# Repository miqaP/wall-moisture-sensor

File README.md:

# wall-moisture-sensor
https://github.com/miqaP/wall-moisture-sensor

# Versionning
Pour le moment j'ai une branche dev. Comment  
- Dev -> Release 

## Version de carte
Il faut se placer du point de vue de la carte et peut-être mettre de côté l'impact sur le firmware

- MAJOR -> Modification importantes -> Changement dans les fonctionnalités du produit -> feat:
    - Ajout d'une fonctionnalitées. Est-ce que l'ajout d'un connecteur est une nouvelle fonctionnalité ? Non je ne crois pas
    - Suppression d'une fonctionnalitées

- MINOR -> Pas de modification de fonctionnalité -> design:
    - Modification de composant, qui necessite la modification du routage par exemple changement de référence d'un DC/DC -> Mais pas de changement dans la fonctionnalité
    - Optimisation du layout, déplacement des composants
    - Changement du layout pour s'intégrer dans un boitier
    - Changement de la sérigraphie
- PATCH -> Modification de la BOM -> bom
    - Ok mais des fois la modification de la BOM implique une modification du firmware, nan ?

# Continuous Integration
Voir https://sschueller.github.io/posts/ci-cd-with-kicad-and-gitlab/
https://github.com/LiveLeds/AstraDriver/tree/main

Liste des commandes qui doivent être lancées par la CI : 
- kicad-cli pcb drc wall_moisture-hardware.kicad_pcb
-  kicad-cli pcb export gerbers wall_moisture-hardware.kicad_pcb -o gerbers/
- kicad-cli render wall_moisture-hardware
- kicad-cli render wall_moisture-hardware.kicad_pcb
- kicad-cli pcb render wall_moisture-hardware.kicad_pcb
- kicad-cli pcb render wall_moisture-hardware.kicad_pcb --output 3drender/top.png -> Il faut faire les autres vues, les orientations et distances de la caméra vont dépendre de la taille du projet. Un script python pourrait determiner ces informations

L'intégration se lance lors de la création d'une release

Chose a réaliser: 
- Un rapport de release qui montre la différence entre la version actuelle et la version précedente -> Voir Kicad-diff
    - Il faut pouvoir détérminer la version précédente, comment faire ?
- Exporter les pdf des schémas et du hardware ( les couches du PCB et la carte complète)

# Note sur la configuration du projet
Commitlint s’exécute à chaque commit grâce au hook Git commit-msg. Ce hook est un script situé dans le dossier .git/hooks/commit-msg qui est automatiquement lancé par Git à la validation d’un commit. Ce script appelle Commitlint pour vérifier que le message du commit respecte les règles définies.

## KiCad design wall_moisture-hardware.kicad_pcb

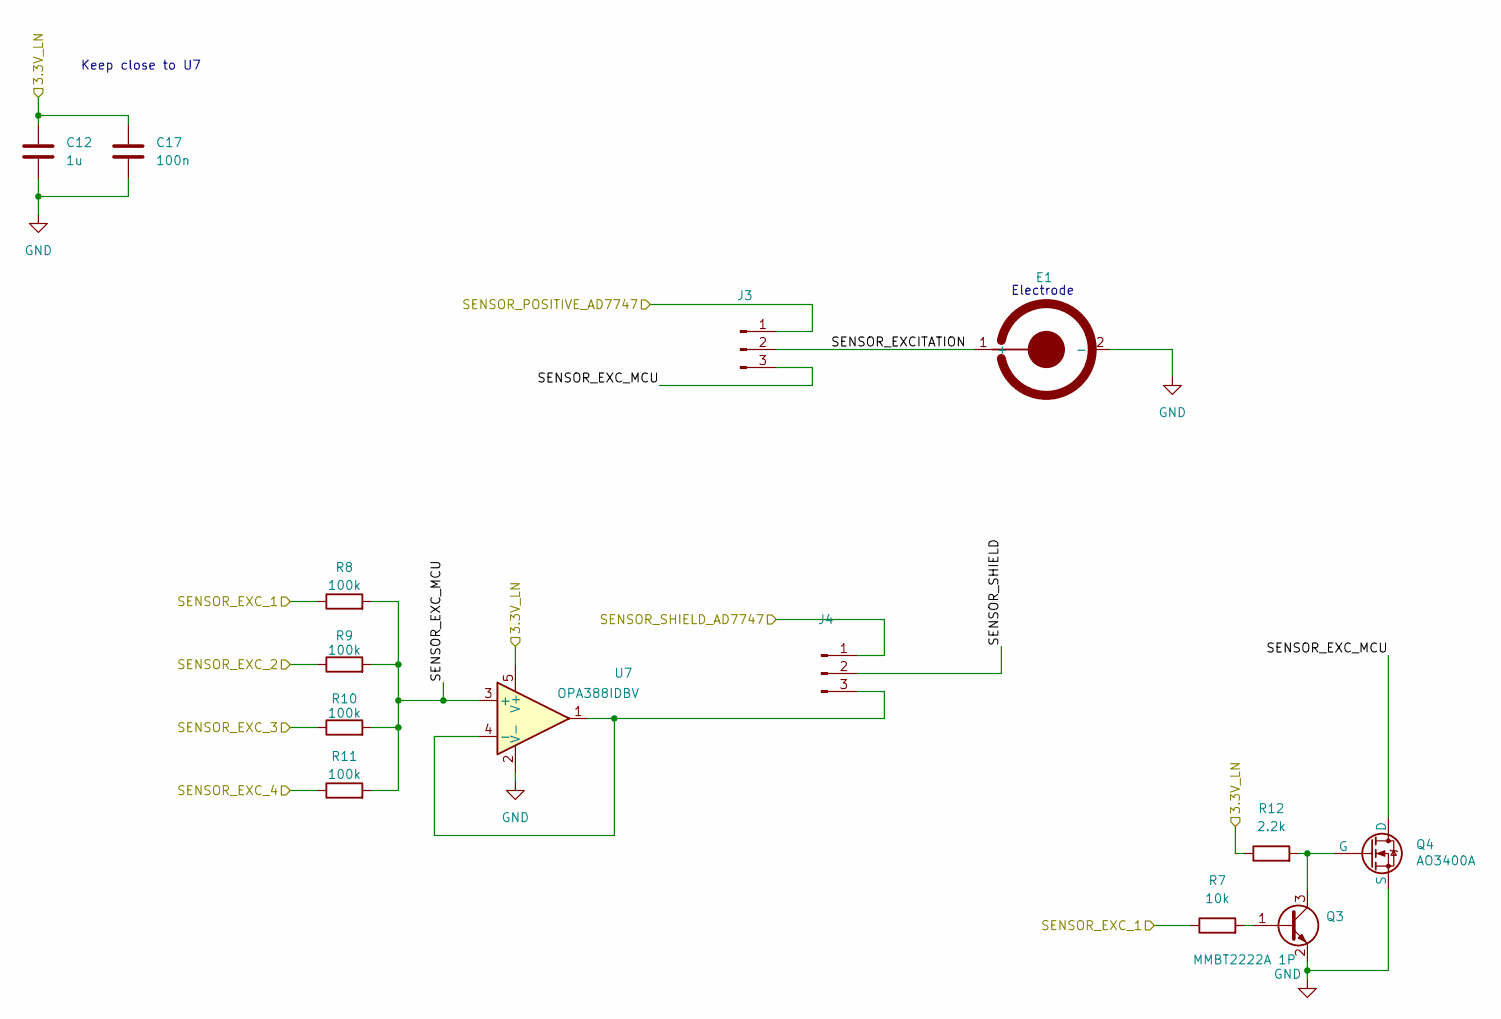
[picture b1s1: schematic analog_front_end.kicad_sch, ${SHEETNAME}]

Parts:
C12: 1u; C_0603_1608Metric; LCSC C15849
C17: 100n; C_0603_1608Metric; LCSC C14663
E1: CapacitiveElectrode-round_20mmx70mm
J3, J4: PinHeader_1x03_P2.54mm_Vertical; MPN 2541WV-03P; LCSC C5383112
Q3: SOT-23; MPN MMBT2222A 1P; LCSC C8512
Q4: SOT-23; MPN AO3400A; LCSC C20917
R7: 10k; R_0603_1608Metric; LCSC C25804
R8, R9, R10, R11: 100k; R_0603_1608Metric; LCSC C25803
R12: 2.2k; R_0603_1608Metric; LCSC C4190
U7: SOT-23-5; MPN OPA388IDBV; LCSC C1850240

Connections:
/Analog frontend/3.3V_LN: C12.1, C17.1, R12.1, U7.5 (V+); also elsewhere on the board
/Analog frontend/SENSOR_EXCITATION: E1.1 (+), J3.2
/Analog frontend/SENSOR_EXC_MCU: J3.3, Q4.1 (D), R8.2, R9.2, R10.2, R11.2, U7.3 (+)
/Analog frontend/SENSOR_POSITIVE_AD7747: J3.1; also elsewhere on the board
/Analog frontend/SENSOR_SHIELD: J4.2
/Analog frontend/SENSOR_SHIELD_AD7747: J4.1; also elsewhere on the board
/µC and digital/TIM1_CH1: R7.1, R8.1; also elsewhere on the board
/µC and digital/TIM1_CH2: R9.1; also elsewhere on the board
/µC and digital/TIM1_CH3: R10.1; also elsewhere on the board
/µC and digital/TIM1_CH4: R11.1; also elsewhere on the board
GND: C12.2, C17.2, E1.2 (-), Q3.2 (E), Q4.3 (S), U7.2 (V-); also elsewhere on the board
unnamed: J4.3, U7.1, U7.4 (-)
unnamed: Q3.1 (B), R7.2
unnamed: Q3.3 (C), Q4.2 (G), R12.2

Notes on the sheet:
Keep close to U7
Electrode

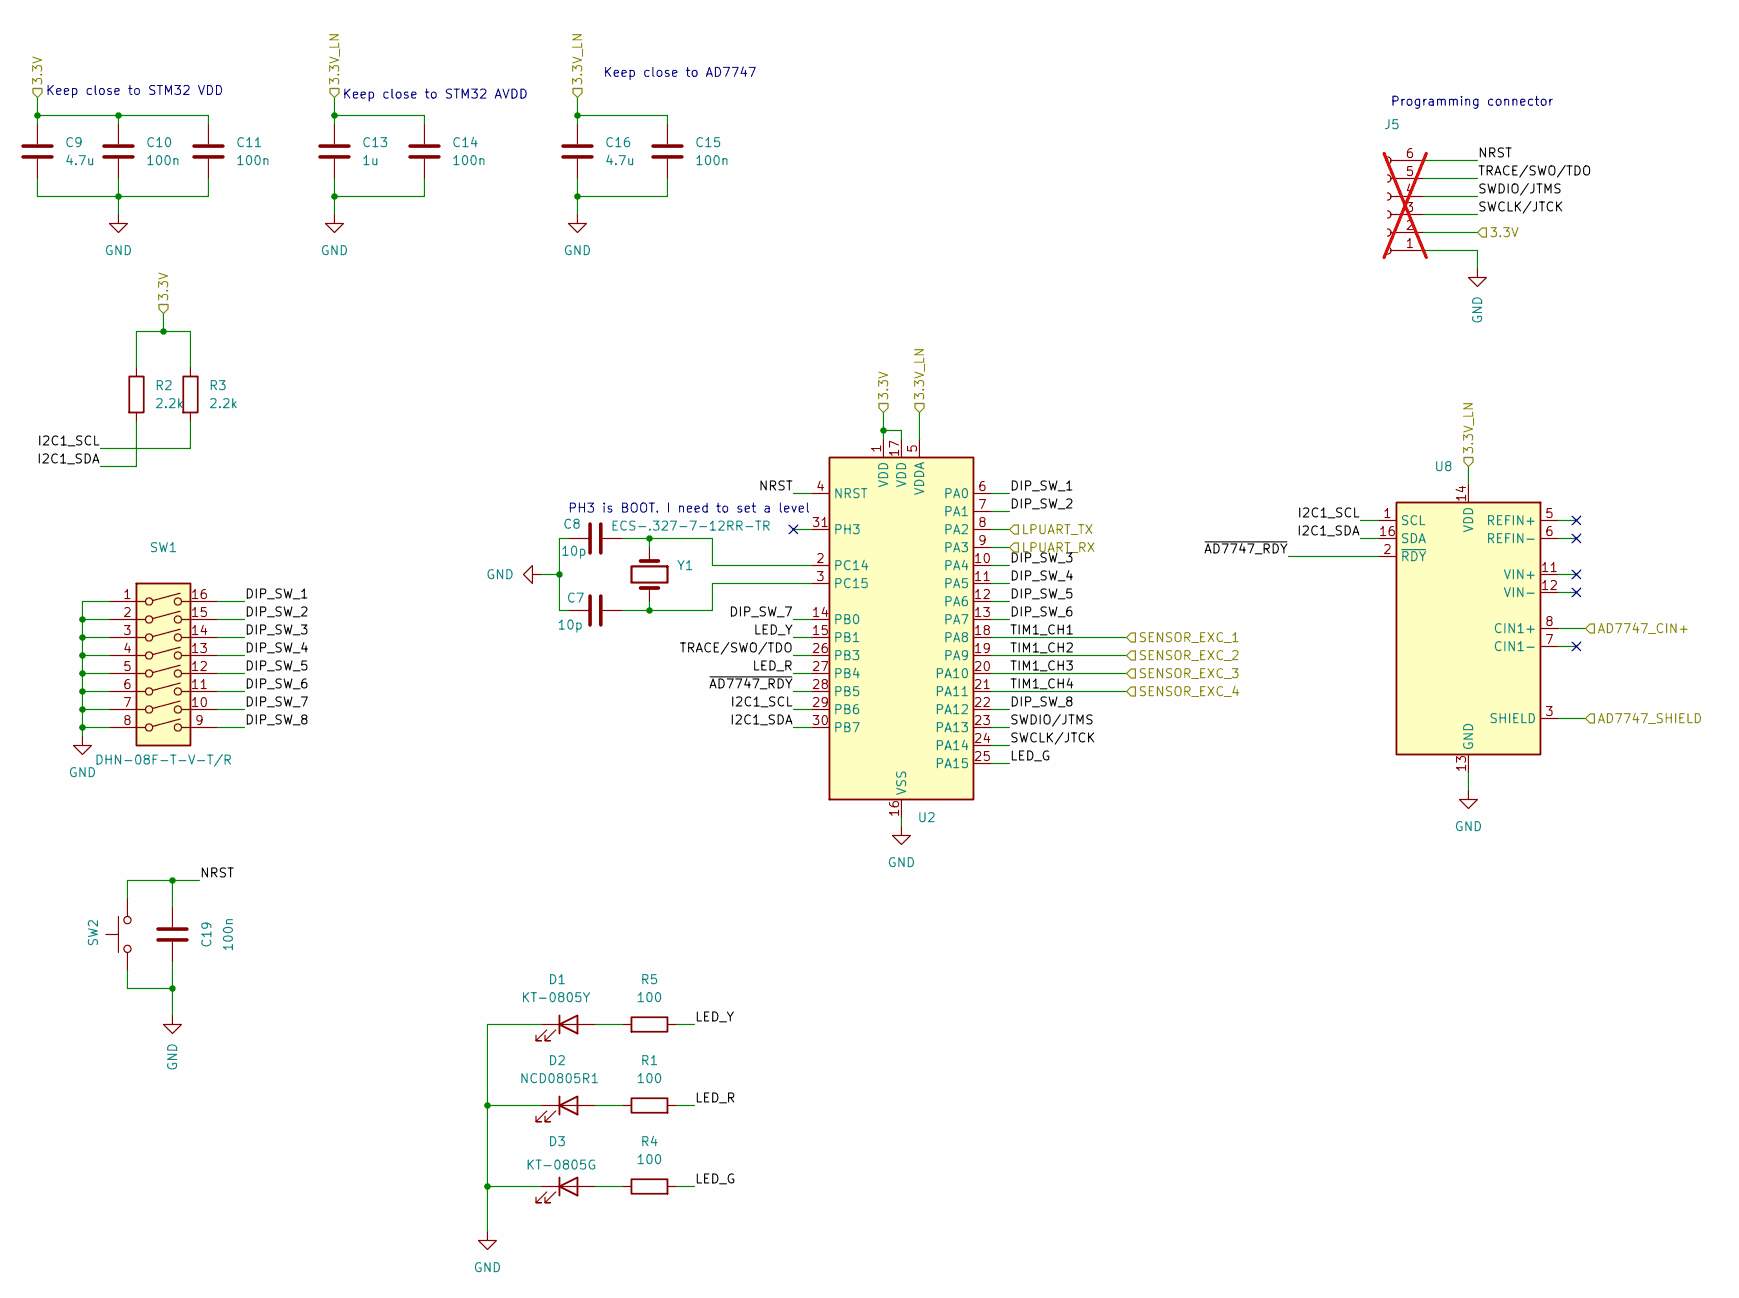
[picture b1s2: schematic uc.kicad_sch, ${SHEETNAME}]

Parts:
C7, C8: 10p; C_0603_1608Metric; LCSC C1634
C9, C16: 4.7u; C_0603_1608Metric; LCSC C19666
C10, C11, C14, C15, C19: 100n; C_0603_1608Metric; LCSC C14663
C13: 1u; C_0603_1608Metric; LCSC C15849
D1: LED_0805_2012Metric; MPN KT-0805Y; LCSC C2296
D2: LED_0805_2012Metric; MPN NCD0805R1; LCSC C84256
D3: LED_0805_2012Metric; MPN KT-0805G; LCSC C2297
J5: Skedd490107670612_2x06_P2.54mm_Debug; MPN 490107670612; not fitted
R1, R4, R5: 100; R_0603_1608Metric; LCSC C22775
R2, R3: 2.2k; R_0603_1608Metric; LCSC C4190
SW1: SW_DIP_SPSTx08_Slide_KingTek_DSHP08TJ_W5.25mm_P1.27mm_JPin; MPN DHN-08F-T-V-T/R; LCSC C89711
SW2: FSMH; SW_Push_1P1T_XKB_TS-1187A; MPN TS-1187A-B-A-B; LCSC C318884
U2: QFN-32-1EP_5x5mm_P0.5mm_EP3.45x3.45mm; MPN STM32L432KBUx; LCSC C2928224
U8: TSSOP-16_4.4x5mm_P0.65mm; MPN AD7747ARUZ; LCSC C578507
Y1: Crystal_SMD_2012-2Pin_2.0x1.2mm; MPN ECS-.327-7-12RR-TR; LCSC C2450089

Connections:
/Analog frontend/3.3V_LN: C13.1, C14.1, C15.1, C16.1, U2.5 (VDDA), U8.14 (VDD); also elsewhere on the board
/Analog frontend/SENSOR_POSITIVE_AD7747: U8.8 (CIN1+); also elsewhere on the board
/Analog frontend/SENSOR_SHIELD_AD7747: U8.3 (SHIELD); also elsewhere on the board
/Connectors and Power/3.3V: C9.1, C10.1, C11.1, J5.2, R2.1, R3.1, U2.1 (VDD), U2.17 (VDD); also elsewhere on the board
/Connectors and Power/MASTER_RX: U2.8 (PA2); also elsewhere on the board
/Connectors and Power/MASTER_TX: U2.9 (PA3); also elsewhere on the board
/µC and digital/DIP_SW_1: SW1.16, U2.6 (PA0)
/µC and digital/DIP_SW_2: SW1.15, U2.7 (PA1)
/µC and digital/DIP_SW_3: SW1.14, U2.10 (PA4)
/µC and digital/DIP_SW_4: SW1.13, U2.11 (PA5)
/µC and digital/DIP_SW_5: SW1.12, U2.12 (PA6)
/µC and digital/DIP_SW_6: SW1.11, U2.13 (PA7)
/µC and digital/DIP_SW_7: SW1.10, U2.14 (PB0)
/µC and digital/DIP_SW_8: SW1.9, U2.22 (PA12)
/µC and digital/I2C1_SCL: R3.2, U2.29 (PB6), U8.1 (SCL)
/µC and digital/I2C1_SDA: R2.2, U2.30 (PB7), U8.16 (SDA)
/µC and digital/LED_G: R4.2, U2.25 (PA15)
/µC and digital/LED_R: R1.2, U2.27 (PB4)
/µC and digital/LED_Y: R5.1, U2.15 (PB1)
/µC and digital/NRST: C19.2, J5.6, SW2.2, U2.4 (NRST)
/µC and digital/SWCLK/JTCK: J5.3, U2.24 (PA14)
/µC and digital/SWDIO/JTMS: J5.4, U2.23 (PA13)
/µC and digital/TIM1_CH1: U2.18 (PA8); also elsewhere on the board
/µC and digital/TIM1_CH2: U2.19 (PA9); also elsewhere on the board
/µC and digital/TIM1_CH3: U2.20 (PA10); also elsewhere on the board
/µC and digital/TIM1_CH4: U2.21 (PA11); also elsewhere on the board
/µC and digital/TRACE/SWO/TDO: J5.5, U2.26 (PB3)
/µC and digital/~AD7747_RDY: U2.28 (PB5), U8.2 (~RDY)
GND: C7.1, C8.1, C9.2, C10.2, C11.2, C13.2, C14.2, C15.2, C16.2, C19.1, D1.1 (K), D2.1 (K), D3.1 (K), J5.1, SW1.1, SW1.2, SW1.3, SW1.4, SW1.5, SW1.6, SW1.7, SW1.8, SW2.1, U2.16 (VSS), U2.32 (VSS), U2.33 (VSS), U8.13 (GND); also elsewhere on the board
unnamed: D1.2 (A), R5.2
unnamed: D2.2 (A), R1.1
unnamed: D3.2 (A), R4.1
unnamed: C8.2, U2.2 (PC14), Y1.1
unnamed: C7.2, U2.3 (PC15), Y1.2

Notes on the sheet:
Keep close to STM32 VDD
Programming connector
Keep close to AD7747
Keep close to STM32 AVDD
PH3 is BOOT. I need to set a level

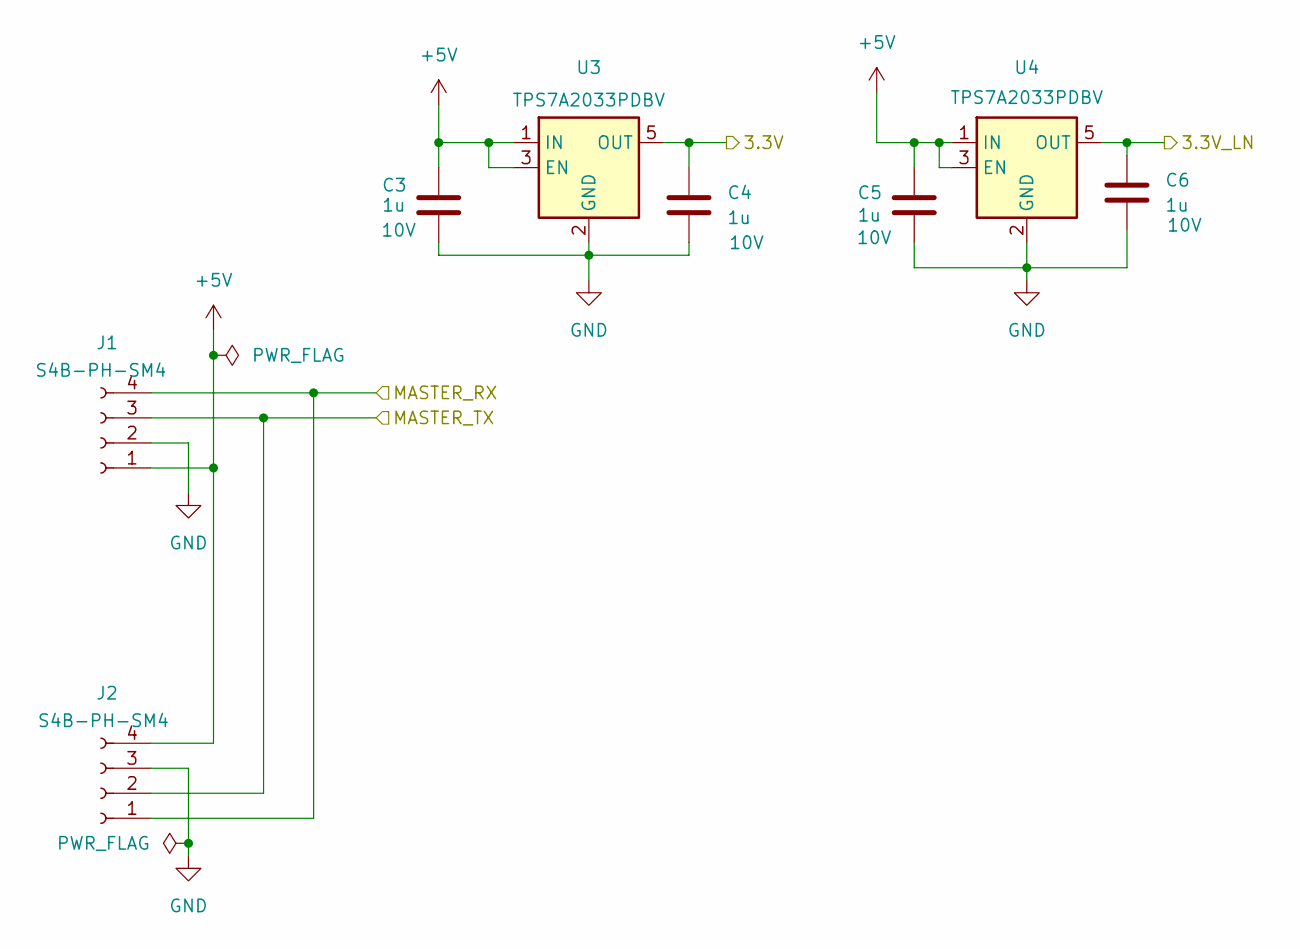
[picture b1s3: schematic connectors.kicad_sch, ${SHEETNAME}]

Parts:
C3, C4, C5, C6: 1u; C_0603_1608Metric; LCSC C15849
J1, J2: JST_PH_S4B-PH-SM4-TB_1x04-1MP_P2.00mm_Horizontal; MPN S4B-PH-SM4; LCSC C265102
U3, U4: SOT-23-5; MPN TPS7A2033PDBV; LCSC C2862740

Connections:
+5V: C3.1, C5.1, J1.1, J2.4, U3.1 (IN), U3.3 (EN), U4.1 (IN), U4.3 (EN)
/Analog frontend/3.3V_LN: C6.1, U4.5 (OUT); also elsewhere on the board
/Connectors and Power/3.3V: C4.1, U3.5 (OUT); also elsewhere on the board
/Connectors and Power/MASTER_RX: J1.4, J2.1; also elsewhere on the board
/Connectors and Power/MASTER_TX: J1.3, J2.2; also elsewhere on the board
GND: C3.2, C4.2, C5.2, C6.2, J1.2, J2.3, U3.2 (GND), U4.2 (GND); also elsewhere on the board

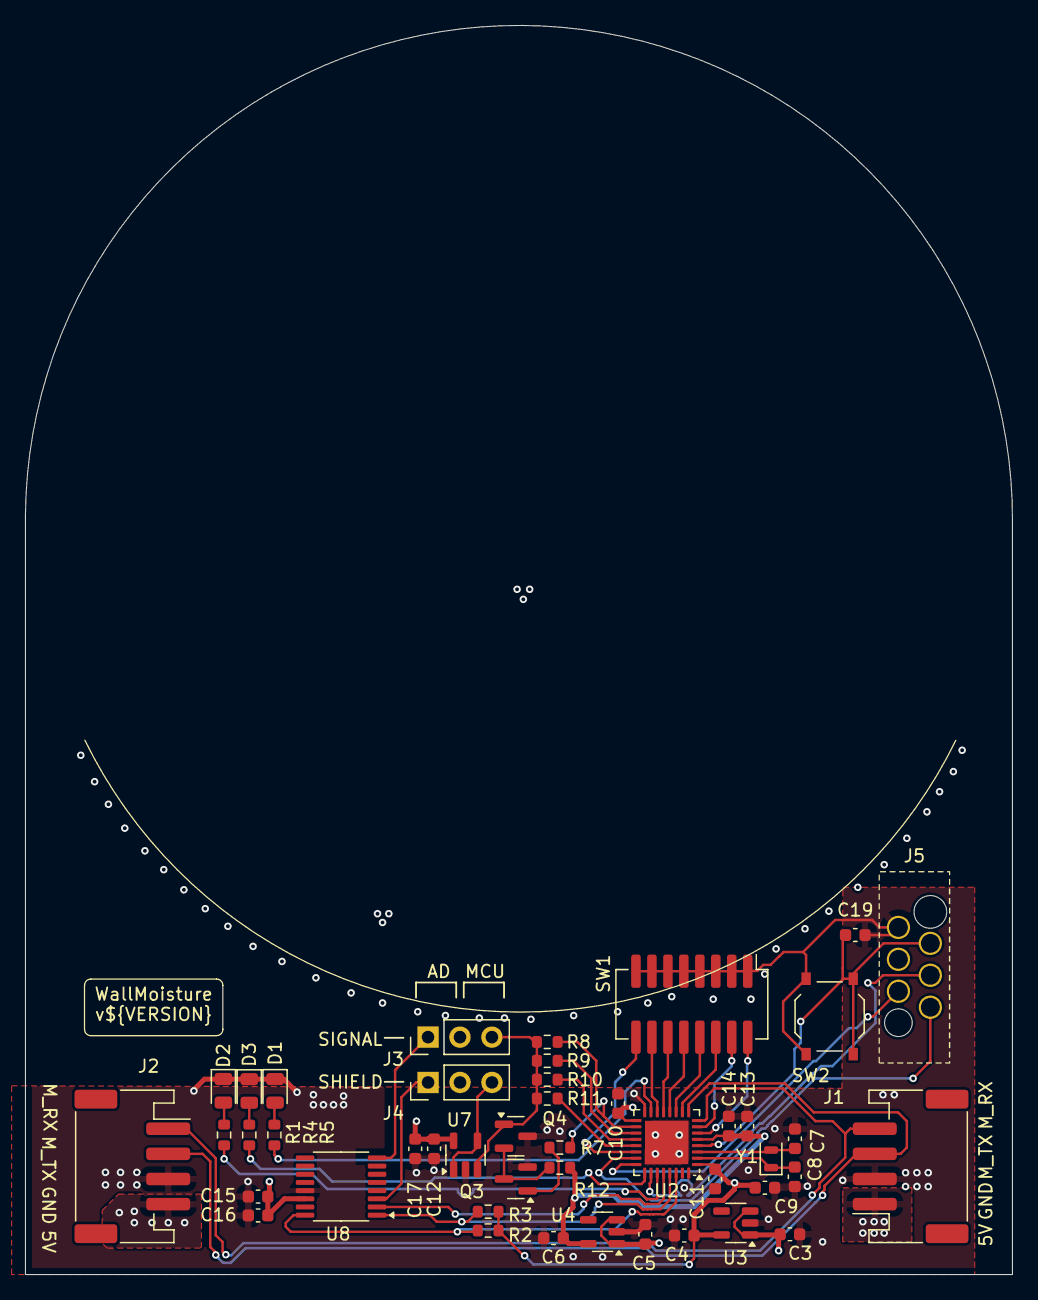
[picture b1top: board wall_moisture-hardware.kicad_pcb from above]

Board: 4 copper layers, 78.5 x 99.3 mm, 46 parts (1 on the bottom side), 40 nets.

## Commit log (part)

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2025-04-05 First commit :
2025-05-05 ci: Initial the CI
    Use https://github.com/LiveLeds/AstraDriver.git as base configuration
2025-05-05 ci: Fix project file path
2025-05-05 ci: Attempt to fix project name variable expansion and add templates
2025-05-05 ci: fix kibot relative paths and upgrade to kibot dk9
2025-05-05 ci: Fix the layer names, change dimensions for drawings
2025-05-05 ci: refactor workflows to place all the 3D render configuration next to each other
2025-05-05 ci: Attempt to fix a variable not expansed while building Jekyll
2025-05-05 ci: fix pcb pdf path
2025-05-05 ci: fix variables not expanded in Jekyll build step
2025-05-06 ci: deploy site on Netlify instead of github pages
2025-05-14 Extract Jekyll and github action configuration from the same project.yml file
2025-05-14 Fix board cutt layer
2025-05-14 Fix variable substitution in Build jekyll step
2025-05-14 Remove theme applied on report step and change the CI to uses kibot instead of running custom script which use SSH key
2025-05-14 Fix CI variable expansion
2025-05-14 ci: remove useless plugin and attempt to fix the variable sharing between the ci and jekyll
2025-05-14 ci: fix path of generated markdown file
2025-05-14 ci: Fix jekyll base url because the site is currently deployed at the root of netlify
2025-05-14 ci: attempt to add renders, schemtics and assembly variants in the project field
2025-05-15 ci: Add actions for others branches
2025-05-15 ci: attempt to add semantic release in ci workflow
2025-05-15 git: update .gitignore to ignore node and gem files
2025-05-15 silk: add board name and placeholder to version number
2025-05-15 ci: fix triggers for github actions
2025-05-15 ci: github action on dev push must fail if errors exist on the DRC / ERC
2025-05-15 ci: allow workflow to complete even on step errors, then summarize failures
2025-05-17 rule-check: Fix the ERC errors and warnings
2025-05-17 ci: Make sure the erc and drc are performed in different ci steps
2025-05-17 ci: filter out some erc warning that are meaning less in ci context
2025-05-17 ci: fix main_actions.yml syntax and give a name to the actions
2025-07-11 ci: configure the npm version to use with .nvmrc file
2025-07-11 ci: configure commitlint to enforce the commit convention defined for kicad projects
2025-07-11 ci: add commitlint ci workflows to enforce the format in ci on each push and each pull request
2025-07-11 design: fix some rules check
2025-07-11 ci: add bom commit type as patch release
2025-07-13 design: complete the routing of the board
2025-07-13 design: fix some erc/drc
2025-07-13 ci: improve the maximum size of commit body length in commitlint configuration
2025-07-13 ci: change the ci to use the latest docker kicad image instead of using the dev image
    It is an attempt to fix the ci showing warning of not matching component between the board and the kicad library
2025-07-13 ci: add package-lock.json to use commitlint during the ci
2025-07-15 chore: fix the naming of connectors sheet file name
2025-07-15 ci: export footprints into the project to avoid lib_fooprint_mismatch warning
2025-07-15 chore: fix the naming of connectors sheet file name and the change the path of footprints
2025-07-15 design: fix electrode footprint that was broken by the import operation
2025-07-16 chore: move the routing inside the sheet frame
2025-07-16 chore: export symbols in project
2025-07-16 chore: update project to use local footprint and symbols
2025-07-16 ci: use only one configuration for erc/drc check in dev and main actions
2025-07-16 design: change mosfet simulation model to use a generic model and useless remove erc exclusion
2025-07-16 ci: use different kibot configuration for independant erc and drc steps
2025-07-17 ci: trigger release action on every pull request not only those which change the pcb
2025-07-17 ci: Fix merging conflict
2025-07-17 ci: Configure the release branch in semantic-release and fix the trigger rule on commitlint
2025-07-18 ci: Don't trigger dev and main actions on test-ci-workflow branch
2025-07-18 ci: Fix semantic-release, it should now work as expected
2025-07-18 Notes added by 'git notes add'
2025-07-18 ci: Fix version substitution in pcb file
2025-07-18 ci: Check ERC and DRC is the same step on release PR and push as they should already be correct
2025-07-18 ci: Remove unused env variable in release PR
2025-07-18 ci: Move semantic-release at the very end of the release push workflow as it must release the project and the website/report
2025-07-18 ci: Merge most of workflow steps in one job
2025-07-18 ci: Upload the website as part of release assets
2025-07-18 ci: Remove deleted steps as buildJekyll dependancy
2025-07-18 ci: Use newer version of github actions
2025-07-18 ci: Fix release push action yml syntax
2025-07-18 ci: Install node before calling semantic-release
2025-07-18 ci: Fix trigger on pull request
2025-07-18 ci: Fix node installation for Semantic Release
2025-07-18 ci: Actually install npm packet
2025-07-18 ci: Attemp to get version from semantic-release
2025-07-18 ci: Propagate the next version to other steps
2025-07-18 ci: Fix artifact semantic branch for push cases
2025-07-18 ci: Some debug
2025-07-18 ci: Update github action permissions to the minimum needed by semantic-release github plugin
2025-07-18 ci: Attempt to fix the assets generation and add change log
2025-07-18 ci: Add prerelease semantic version
2025-07-18 ci: Should fix the pcb centering issue, and use some correct layer for rendering
2025-07-18 ci: Remove some useless print on release PR actions
2025-07-19 ci: Create release branch
2025-07-19 ci: Add release notes generator plugin on semantic-release
2025-07-19 ci: Fix step configuration file name
2025-07-19 ci: Move jekyll site in its own repository
2025-07-19 ci: Remove the limit on the number of commit KiRi may compare
2025-07-19 ci: Remove step generation that was generated both time
2025-07-19 ci: Move md file used by jekyll site into the jekyll to make them available when building the site
2025-07-19 ci: Move all the required documents in the site into a site directory, it avoid to clutter the site with useless files
2025-07-20 ci: Move generic Jekyll configuration in git repository, https://github.com/miqaP/kicad-jekyll-report
2025-07-20 ci: Use the kicad-jekyll-report dev branch for testing purposes
2025-07-20 ci: Switch releases-notes-generator preset to conventionalcommits in order to correctly parse my commit message which are sentence-case
2025-07-20 ci: Fix the commit parsing
2025-07-20 ci: Add the project version in jekyll generate site, also rename the site zip file with its version number
2025-07-20 design: Fix the 3d model used by crystal Y1
2025-07-20 feature: Add docker script and yml configuration to export 3d into the project, in order to create a self contained project
2025-07-20 design: Add the component 3d model to the repository, it allows to generate 3d image and step with components populated
2025-07-20 design: Fix DRC error
2025-07-20 ci: Fix project.yml structure and provide explicit installation for semantic-release
2025-07-20 ci: Fix push github action to not trigger on pull request which is not working because semantic-release expect to be executed from push action
2025-07-20 design: Fix DRC error, I had to downgrade my kicad version to the version used by kibot
2025-07-20 ci: Fix path to jekyll site during build
2025-07-20 ci: Set the KIBOT_3D_MODELS to point to the 3d models directory, this directory will be used to fetch the model from
2025-07-20 ci: Add missing package requiered by semantic-release
2025-07-20 ci: Fix the env variable name to point to 3d models directory
2025-07-20 ci: Change output folder name for KiRi because jekyll will lower case the folder which seems to broke the KiRi pages
2025-07-20 ci: Debug of KiRi pages not working
2025-07-20 ci: Revert debug configuration
2025-07-20 ci: Ignore locally kibot generated file from repository
2025-07-20 ci: Include hidden files (e.g dot files) when uploading kibot reports artifacts
    This is mandatory for KiRi because it generate dot files that are required for correct working
2025-07-24 design: Assign LSCS and MPN reference to components
2025-07-24 design: Assign the project version and project company from project variable, which are then substituted during the ci
2025-07-24 design: Apply the change in schematic sheet name on pcb file
2025-07-24 ci: Renders are exported in their home directory using better file naming
2025-07-24 ci: Fix missing fields in interactive bom
2025-07-24 ci: Lower case and harmonise output, directory and files names
2025-07-24 ci: Add kibot configuration to assert all required fields are populated and no additionnal fields have been added
2025-07-24 ci: Set company name in project configuration, it is substitued in kicad files in order to print it in generated documents
2025-07-24 ci: Change eurocircuits_class_target to better fit with their actual defauts specification
2025-07-24 ci: Trigger the actions on pull request and by pass semantic-release (which need to be run on push actions) to test the ci workflow
2025-07-24 ci: Some additionnal file name harmonization
2025-07-24 ci: Add provide the GitHub repository link to jekyll and remove the 'just the docs' link
2025-07-24 design: Fix DRC errors
2025-07-24 design: Add subsistute text for text variables
2025-07-24 ci: Fix the text substitution command
2025-07-24 ci: Fix name of jlcpcb manufacturing configuration
2025-07-24 ci: Fix renders artifact name
2025-07-24 ci: Apply refactoring on release push action
2025-07-24 ci: Remove the github action on push on dev branches because this is useless
2025-07-24 ci: Remove the KiRi local commit that brokes the page
2025-07-24 ci: Fix KiRi commits cleaning
2025-07-29 chore: Create release branch
2025-07-29 chore: Create main branch
2025-07-29 ci: Configure commitlint for KiCAD project
2025-07-29 ci: Configure semantic-release for KiCAD project
2025-07-29 chore: Create test-ci-workflow branch
2025-07-29 chore: Create test-ci-workflow-pre branch
2025-07-29 ci: Add pull request action for ci workflow
2025-07-29 ci: Add push action for ci workflow
2025-07-29 design: Shield excitation signal and exclude poor planes around the signal trace
    Excluding poor plane around the signal should reduce the capacitive parasitance.
    Shield is now protecting the signal trace that goes to the electrode
2025-07-29 chore: Add script to start kibot in docker and add kibot configuration that extract the 3d models
2025-07-29 ci: Run commitlint on pull request on every branches
2025-07-29 ci: Use the kibot dev image during sanatize_bom checks as it depends of filters feature that is not yet available in latest image
2025-07-29 design: Align interface connectors
2025-07-30 design: Fix signal shielding
    - Continue the shield up to the signal start point
    - Move the copper plan that connect sensor to the signal on the correct layer
2025-07-30 design: Fix signal shielding, move copper pour connecting signal and sensor to the correct layer
2025-07-30 design: Move vias to enhance the 5V copper fill continuity and reduce the impedance
2025-07-30 ci: Fix some parts orientation and offsets
2025-07-30 bom: Optimize part selection to reduce order price at jlcpcb
    - Change references to use basic components instead of 'extended components' when available
    - Change button reference to use a basic component
    - Change led references to use basic components
    - Harmonize some resistors value to limit the number of lines in BoM
    - Change transistor references for basic components
2025-07-30 design: Propagate the changes to the PCB and change the tactile switch footprint
2025-07-31 bom: Fix the SW1 dip switch reference
    Select a part that fit the footprint
2025-07-31 chore: Add date current date in page setting
2025-07-31 silk: Document the jumper functionality and label the connector signal names
2025-07-31 chore: Use jlcpcb DRC constraints on silk layer and apply change the board to comply with the constraints
